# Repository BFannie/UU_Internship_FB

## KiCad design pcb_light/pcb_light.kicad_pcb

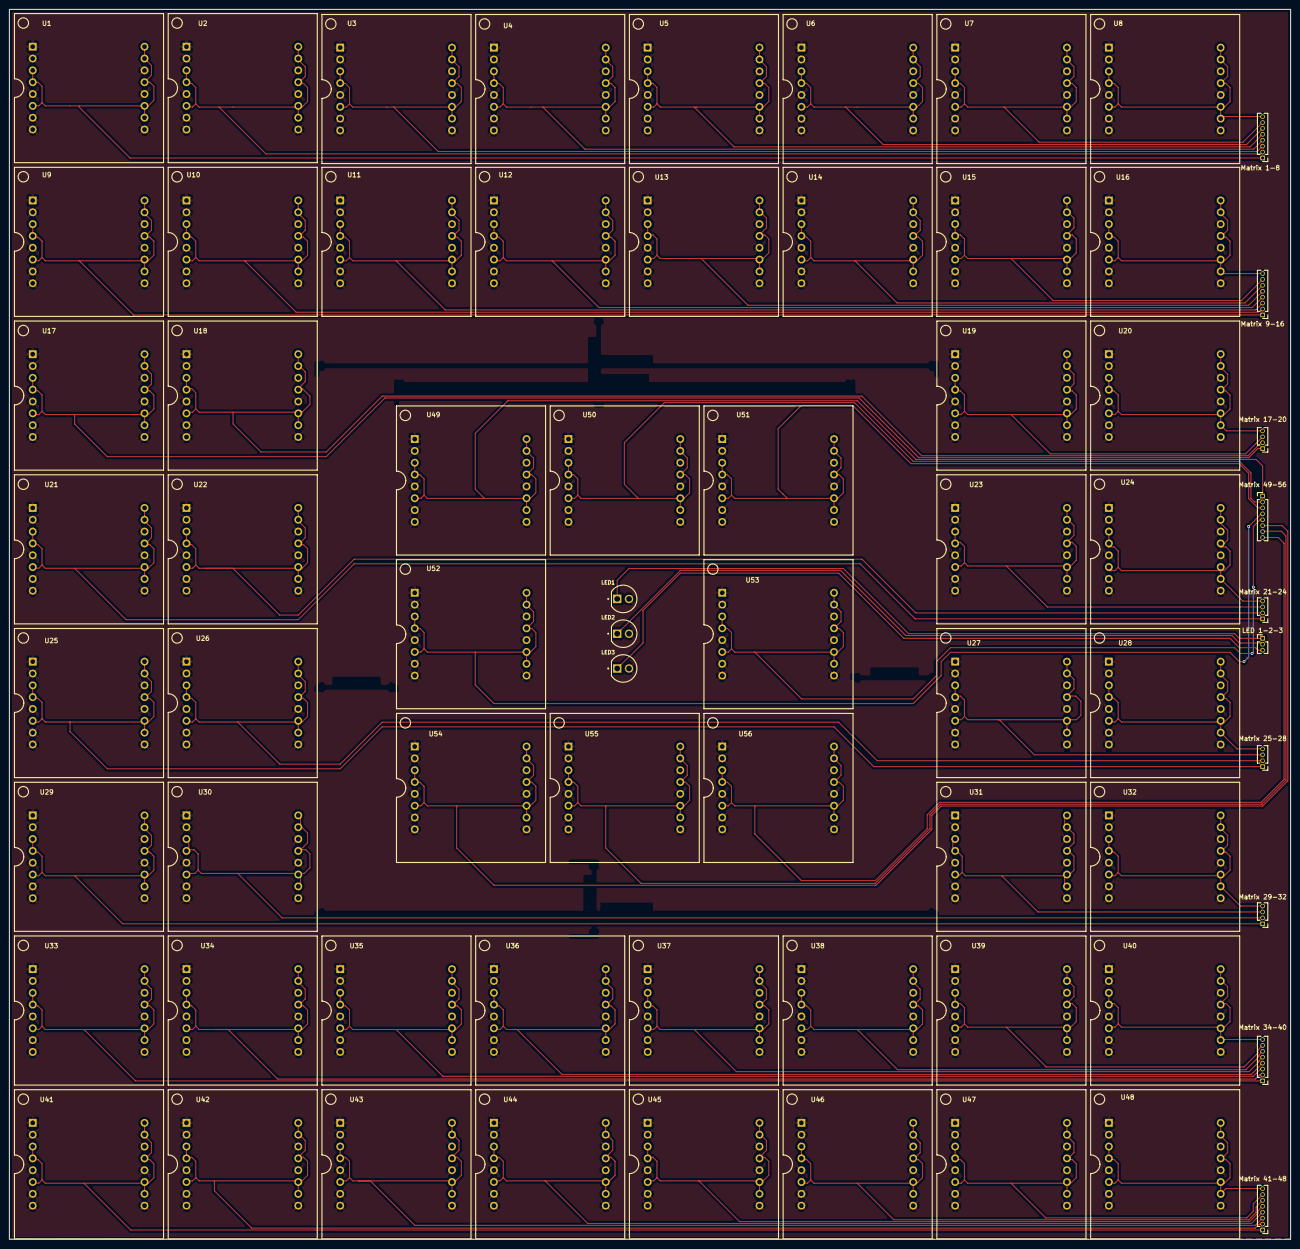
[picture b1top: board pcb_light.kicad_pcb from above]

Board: 2 copper layers, 275.0 x 264.0 mm, 69 parts (0 on the bottom side), 60 nets.

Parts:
 Matrix 1-8,  Matrix 9-16,  Matrix 34-40,  Matrix 41-48,  Matrix 49-56: Conn_01x08_Pin; PinHeader_1x08_P1.27mm_Vertical
 Matrix 17-20: Matrix 17-20; PinHeader_1x04_P1.27mm_Vertical
 Matrix 21-24,  Matrix 25-28,  Matrix 29-32: Conn_01x04_Pin; PinHeader_1x04_P1.27mm_Vertical
LED1, LED2, LED3: L08R5000Q1; LEDRD254W57D500H1070
LED 1-2-3: Conn_01x03_Pin; PinHeader_1x03_P1.27mm_Vertical
U1, U2, U3, U4, U5, U6, U7, U8, U9, U10, U11, U12, U13, U14, U15, U16, U17, U18, U19, U20, U21, U22, U23, U24, U25, U26, U27, U28, U29, U30, U31, U32, U33, U34, U35, U36, U37, U38, U39, U40, U41, U42, U43, U44, U45, U46, U47, U48, U49, U50, U51, U52, U53, U54, U55, U56: 1088BS; LED_1088_Pin_Header

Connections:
GND: LED1.A, LED2.A, LED3.A, U1.1 (C4), U1.2 (C2), U1.5 (C1), U1.7 (C3), U1.8 (C6), U1.9 (C8), U1.12 (C5), U1.14 (C7), U2.1 (C4), U2.2 (C2), U2.5 (C1), U2.7 (C3), U2.8 (C6), U2.9 (C8), U2.12 (C5), U2.14 (C7), U3.1 (C4), U3.2 (C2), U3.5 (C1), U3.7 (C3), U3.8 (C6), U3.9 (C8), U3.12 (C5), U3.14 (C7), U4.1 (C4), U4.2 (C2), U4.5 (C1), U4.7 (C3), U4.8 (C6), U4.9 (C8), U4.12 (C5), U4.14 (C7), U5.1 (C4), U5.2 (C2), U5.5 (C1), U5.7 (C3), U5.8 (C6), U5.9 (C8), U5.12 (C5), U5.14 (C7), U6.1 (C4), U6.2 (C2), U6.5 (C1), U6.7 (C3), U6.8 (C6), U6.9 (C8), U6.12 (C5), U6.14 (C7), U7.1 (C4), U7.2 (C2), U7.5 (C1), U7.7 (C3), U7.8 (C6), U7.9 (C8), U7.12 (C5), U7.14 (C7), U8.1 (C4), U8.2 (C2), U8.5 (C1), U8.7 (C3), U8.8 (C6), U8.9 (C8), U8.12 (C5), U8.14 (C7), U9.1 (C4), U9.2 (C2), U9.5 (C1), U9.7 (C3), U9.8 (C6), U9.9 (C8), U9.12 (C5), U9.14 (C7), U10.1 (C4), U10.2 (C2), U10.5 (C1), U10.7 (C3), U10.8 (C6), U10.9 (C8), U10.12 (C5), U10.14 (C7), U11.1 (C4), U11.2 (C2), U11.5 (C1), U11.7 (C3), U11.8 (C6), U11.9 (C8), U11.12 (C5), U11.14 (C7), U12.1 (C4), U12.2 (C2), U12.5 (C1), U12.7 (C3), U12.8 (C6), U12.9 (C8), U12.12 (C5), U12.14 (C7), U13.1 (C4), U13.2 (C2), U13.5 (C1), U13.7 (C3), U13.8 (C6), U13.9 (C8), U13.12 (C5), U13.14 (C7), U14.1 (C4), U14.2 (C2), U14.5 (C1), U14.7 (C3), U14.8 (C6), U14.9 (C8), U14.12 (C5), U14.14 (C7), U15.1 (C4), U15.2 (C2), U15.5 (C1), U15.7 (C3), U15.8 (C6), U15.9 (C8), U15.12 (C5), U15.14 (C7), U16.1 (C4), U16.2 (C2), U16.5 (C1), U16.7 (C3), U16.8 (C6), U16.9 (C8), U16.12 (C5), U16.14 (C7), U17.1 (C4), U17.2 (C2), U17.5 (C1), U17.7 (C3), U17.8 (C6), U17.9 (C8), U17.12 (C5), U17.14 (C7), U18.1 (C4), U18.2 (C2), U18.5 (C1), U18.7 (C3), U18.8 (C6), U18.9 (C8), U18.12 (C5), U18.14 (C7), U19.1 (C4), U19.2 (C2), U19.5 (C1), U19.7 (C3), U19.8 (C6), U19.9 (C8), U19.12 (C5), U19.14 (C7), U20.1 (C4), U20.2 (C2), U20.5 (C1), U20.7 (C3), U20.8 (C6), U20.9 (C8), U20.12 (C5), U20.14 (C7), U21.1 (C4), U21.2 (C2), U21.5 (C1), U21.7 (C3), U21.8 (C6), U21.9 (C8), U21.12 (C5), U21.14 (C7), U22.1 (C4), U22.2 (C2), U22.5 (C1), U22.7 (C3), U22.8 (C6), U22.9 (C8), U22.12 (C5), U22.14 (C7), U23.1 (C4), U23.2 (C2), U23.5 (C1), U23.7 (C3), U23.8 (C6), U23.9 (C8), U23.12 (C5), U23.14 (C7), U24.1 (C4), U24.2 (C2), U24.5 (C1), U24.7 (C3), U24.8 (C6), U24.9 (C8), U24.12 (C5), U24.14 (C7), U25.1 (C4), U25.2 (C2), U25.5 (C1), U25.7 (C3), U25.8 (C6), U25.9 (C8), U25.12 (C5), U25.14 (C7), U26.1 (C4), U26.2 (C2), U26.5 (C1), U26.7 (C3), U26.8 (C6), U26.9 (C8), U26.12 (C5), U26.14 (C7), U27.1 (C4), U27.2 (C2), U27.5 (C1), U27.7 (C3), U27.8 (C6), U27.9 (C8), U27.12 (C5), U27.14 (C7), U28.1 (C4), U28.2 (C2), U28.5 (C1), U28.7 (C3), U28.8 (C6), U28.9 (C8), U28.12 (C5), U28.14 (C7), U29.1 (C4), U29.2 (C2), U29.5 (C1), U29.7 (C3), U29.8 (C6), U29.9 (C8), U29.12 (C5), U29.14 (C7), U30.1 (C4), U30.2 (C2), U30.5 (C1), U30.7 (C3), U30.8 (C6), U30.9 (C8), U30.12 (C5), U30.14 (C7), U31.1 (C4), U31.2 (C2), U31.5 (C1), U31.7 (C3), U31.8 (C6), U31.9 (C8), U31.12 (C5), U31.14 (C7), U32.1 (C4), U32.2 (C2), U32.5 (C1), U32.7 (C3), U32.8 (C6), U32.9 (C8), U32.12 (C5), U32.14 (C7), U33.1 (C4), U33.2 (C2), U33.5 (C1), U33.7 (C3), U33.8 (C6), U33.9 (C8), U33.12 (C5), U33.14 (C7), U34.1 (C4), U34.2 (C2), U34.5 (C1), U34.7 (C3), U34.8 (C6), U34.9 (C8), U34.12 (C5), U34.14 (C7), U35.1 (C4), U35.2 (C2), U35.5 (C1), U35.7 (C3), U35.8 (C6), U35.9 (C8), U35.12 (C5), U35.14 (C7), U36.1 (C4), U36.2 (C2), U36.5 (C1), U36.7 (C3), U36.8 (C6), U36.9 (C8), U36.12 (C5), U36.14 (C7), U37.1 (C4), U37.2 (C2), U37.5 (C1), U37.7 (C3), U37.8 (C6), U37.9 (C8), U37.12 (C5), U37.14 (C7), U38.1 (C4), U38.2 (C2), U38.5 (C1), U38.7 (C3), U38.8 (C6), U38.9 (C8), U38.12 (C5), U38.14 (C7), U39.1 (C4), U39.2 (C2), U39.5 (C1), U39.7 (C3), U39.8 (C6), U39.9 (C8), U39.12 (C5), U39.14 (C7), U40.1 (C4), U40.2 (C2), U40.5 (C1), U40.7 (C3), U40.8 (C6), U40.9 (C8), U40.12 (C5), U40.14 (C7), U41.1 (C4), U41.2 (C2), U41.5 (C1), U41.7 (C3), U41.8 (C6), U41.9 (C8), U41.12 (C5), U41.14 (C7), U42.1 (C4), U42.2 (C2), U42.5 (C1), U42.7 (C3), U42.8 (C6), U42.9 (C8), U42.12 (C5), U42.14 (C7), U43.1 (C4), U43.2 (C2), U43.5 (C1), U43.7 (C3), U43.8 (C6), U43.9 (C8), U43.12 (C5), U43.14 (C7), U44.1 (C4), U44.2 (C2), U44.5 (C1), U44.7 (C3), U44.8 (C6), U44.9 (C8), U44.12 (C5), U44.14 (C7), U45.1 (C4), U45.2 (C2), U45.5 (C1), U45.7 (C3), U45.8 (C6), U45.9 (C8), U45.12 (C5), U45.14 (C7), U46.1 (C4), U46.2 (C2), U46.5 (C1), U46.7 (C3), U46.8 (C6), U46.9 (C8), U46.12 (C5), U46.14 (C7), U47.1 (C4), U47.2 (C2), U47.5 (C1), U47.7 (C3), U47.8 (C6), U47.9 (C8), U47.12 (C5), U47.14 (C7), U48.1 (C4), U48.2 (C2), U48.5 (C1), U48.7 (C3), U48.8 (C6), U48.9 (C8), U48.12 (C5), U48.14 (C7), U49.1 (C4), U49.2 (C2), U49.5 (C1), U49.7 (C3), U49.8 (C6), U49.9 (C8), U49.12 (C5), U49.14 (C7), U50.1 (C4), U50.2 (C2), U50.5 (C1), U50.7 (C3), U50.8 (C6), U50.9 (C8), U50.12 (C5), U50.14 (C7), U51.1 (C4), U51.2 (C2), U51.5 (C1), U51.7 (C3), U51.8 (C6), U51.9 (C8), U51.12 (C5), U51.14 (C7), U52.1 (C4), U52.2 (C2), U52.5 (C1), U52.7 (C3), U52.8 (C6), U52.9 (C8), U52.12 (C5), U52.14 (C7), U53.1 (C4), U53.2 (C2), U53.5 (C1), U53.7 (C3), U53.8 (C6), U53.9 (C8), U53.12 (C5), U53.14 (C7), U54.1 (C4), U54.2 (C2), U54.5 (C1), U54.7 (C3), U54.8 (C6), U54.9 (C8), U54.12 (C5), U54.14 (C7), U55.1 (C4), U55.2 (C2), U55.5 (C1), U55.7 (C3), U55.8 (C6), U55.9 (C8), U55.12 (C5), U55.14 (C7), U56.1 (C4), U56.2 (C2), U56.5 (C1), U56.7 (C3), U56.8 (C6), U56.9 (C8), U56.12 (C5), U56.14 (C7)
Kath_led1: LED1.C, LED 1-2-3.1
Kath_led2: LED2.C, LED 1-2-3.2
Kath_led3: LED3.C, LED 1-2-3.3
kath_1: Matrix 1-8.1, U1.3 (R2), U1.4 (R3), U1.6 (R5), U1.10 (R4), U1.11 (R6), U1.13 (R1), U1.15 (R7), U1.16 (R8)
kath_2: Matrix 1-8.2, U2.3 (R2), U2.4 (R3), U2.6 (R5), U2.10 (R4), U2.11 (R6), U2.13 (R1), U2.15 (R7), U2.16 (R8)
kath_3: Matrix 1-8.3, U3.3 (R2), U3.4 (R3), U3.6 (R5), U3.10 (R4), U3.11 (R6), U3.13 (R1), U3.15 (R7), U3.16 (R8)
kath_4: Matrix 1-8.4, U4.3 (R2), U4.4 (R3), U4.6 (R5), U4.10 (R4), U4.11 (R6), U4.13 (R1), U4.15 (R7), U4.16 (R8)
kath_5: Matrix 1-8.5, U5.3 (R2), U5.4 (R3), U5.6 (R5), U5.10 (R4), U5.11 (R6), U5.13 (R1), U5.15 (R7), U5.16 (R8)
kath_6: Matrix 1-8.6, U6.3 (R2), U6.4 (R3), U6.6 (R5), U6.10 (R4), U6.11 (R6), U6.13 (R1), U6.15 (R7), U6.16 (R8)
kath_7: Matrix 1-8.7, U7.3 (R2), U7.4 (R3), U7.6 (R5), U7.10 (R4), U7.11 (R6), U7.13 (R1), U7.15 (R7), U7.16 (R8)
kath_8: Matrix 1-8.8, U8.3 (R2), U8.4 (R3), U8.6 (R5), U8.10 (R4), U8.11 (R6), U8.13 (R1), U8.15 (R7), U8.16 (R8)
kath_9: Matrix 9-16.1, U9.3 (R2), U9.4 (R3), U9.6 (R5), U9.10 (R4), U9.11 (R6), U9.13 (R1), U9.15 (R7), U9.16 (R8)
kath_10: Matrix 9-16.2, U10.3 (R2), U10.4 (R3), U10.6 (R5), U10.10 (R4), U10.11 (R6), U10.13 (R1), U10.15 (R7), U10.16 (R8)
kath_11: Matrix 9-16.3, U11.3 (R2), U11.4 (R3), U11.6 (R5), U11.10 (R4), U11.11 (R6), U11.13 (R1), U11.15 (R7), U11.16 (R8)
kath_12: Matrix 9-16.4, U12.3 (R2), U12.4 (R3), U12.6 (R5), U12.10 (R4), U12.11 (R6), U12.13 (R1), U12.15 (R7), U12.16 (R8)
kath_13: Matrix 9-16.5, U13.3 (R2), U13.4 (R3), U13.6 (R5), U13.10 (R4), U13.11 (R6), U13.13 (R1), U13.15 (R7), U13.16 (R8)
kath_14: Matrix 9-16.6, U14.3 (R2), U14.4 (R3), U14.6 (R5), U14.10 (R4), U14.11 (R6), U14.13 (R1), U14.15 (R7), U14.16 (R8)
kath_15: Matrix 9-16.7, U15.3 (R2), U15.4 (R3), U15.6 (R5), U15.10 (R4), U15.11 (R6), U15.13 (R1), U15.15 (R7), U15.16 (R8)
kath_16: Matrix 9-16.8, U16.3 (R2), U16.4 (R3), U16.6 (R5), U16.10 (R4), U16.11 (R6), U16.13 (R1), U16.15 (R7), U16.16 (R8)
kath_17: Matrix 17-20.1, U17.3 (R2), U17.4 (R3), U17.6 (R5), U17.10 (R4), U17.11 (R6), U17.13 (R1), U17.15 (R7), U17.16 (R8)
kath_18: Matrix 17-20.2, U18.3 (R2), U18.4 (R3), U18.6 (R5), U18.10 (R4), U18.11 (R6), U18.13 (R1), U18.15 (R7), U18.16 (R8)
kath_19: Matrix 17-20.3, U19.3 (R2), U19.4 (R3), U19.6 (R5), U19.10 (R4), U19.11 (R6), U19.13 (R1), U19.15 (R7), U19.16 (R8)
kath_20: Matrix 17-20.4, U20.3 (R2), U20.4 (R3), U20.6 (R5), U20.10 (R4), U20.11 (R6), U20.13 (R1), U20.15 (R7), U20.16 (R8)
kath_21: Matrix 21-24.1, U21.3 (R2), U21.4 (R3), U21.6 (R5), U21.10 (R4), U21.11 (R6), U21.13 (R1), U21.15 (R7), U21.16 (R8)
kath_22: Matrix 21-24.2, U22.3 (R2), U22.4 (R3), U22.6 (R5), U22.10 (R4), U22.11 (R6), U22.13 (R1), U22.15 (R7), U22.16 (R8)
kath_23: Matrix 21-24.3, U23.3 (R2), U23.4 (R3), U23.6 (R5), U23.10 (R4), U23.11 (R6), U23.13 (R1), U23.15 (R7), U23.16 (R8)
kath_24: Matrix 21-24.4, U24.3 (R2), U24.4 (R3), U24.6 (R5), U24.10 (R4), U24.11 (R6), U24.13 (R1), U24.15 (R7), U24.16 (R8)
kath_25: Matrix 25-28.1, U25.3 (R2), U25.4 (R3), U25.6 (R5), U25.10 (R4), U25.11 (R6), U25.13 (R1), U25.15 (R7), U25.16 (R8)
kath_26: Matrix 25-28.2, U26.3 (R2), U26.4 (R3), U26.6 (R5), U26.10 (R4), U26.11 (R6), U26.13 (R1), U26.15 (R7), U26.16 (R8)
kath_27: Matrix 25-28.3, U27.3 (R2), U27.4 (R3), U27.6 (R5), U27.10 (R4), U27.11 (R6), U27.13 (R1), U27.15 (R7), U27.16 (R8)
kath_28: Matrix 25-28.4, U28.3 (R2), U28.4 (R3), U28.6 (R5), U28.10 (R4), U28.11 (R6), U28.13 (R1), U28.15 (R7), U28.16 (R8)
kath_29: Matrix 29-32.1, U29.3 (R2), U29.4 (R3), U29.6 (R5), U29.10 (R4), U29.11 (R6), U29.13 (R1), U29.15 (R7), U29.16 (R8)
kath_30: Matrix 29-32.2, U30.3 (R2), U30.4 (R3), U30.6 (R5), U30.10 (R4), U30.11 (R6), U30.13 (R1), U30.15 (R7), U30.16 (R8)
kath_31: Matrix 29-32.3, U31.3 (R2), U31.4 (R3), U31.6 (R5), U31.10 (R4), U31.11 (R6), U31.13 (R1), U31.15 (R7), U31.16 (R8)
kath_32: Matrix 29-32.4, U32.3 (R2), U32.4 (R3), U32.6 (R5), U32.10 (R4), U32.11 (R6), U32.13 (R1), U32.15 (R7), U32.16 (R8)
kath_33: Matrix 34-40.1, U33.3 (R2), U33.4 (R3), U33.6 (R5), U33.10 (R4), U33.11 (R6), U33.13 (R1), U33.15 (R7), U33.16 (R8)
kath_34: Matrix 34-40.2, U34.3 (R2), U34.4 (R3), U34.6 (R5), U34.10 (R4), U34.11 (R6), U34.13 (R1), U34.15 (R7), U34.16 (R8)
kath_35: Matrix 34-40.3, U35.3 (R2), U35.4 (R3), U35.6 (R5), U35.10 (R4), U35.11 (R6), U35.13 (R1), U35.15 (R7), U35.16 (R8)
kath_36: Matrix 34-40.4, U36.3 (R2), U36.4 (R3), U36.6 (R5), U36.10 (R4), U36.11 (R6), U36.13 (R1), U36.15 (R7), U36.16 (R8)
kath_37: Matrix 34-40.5, U37.3 (R2), U37.4 (R3), U37.6 (R5), U37.10 (R4), U37.11 (R6), U37.13 (R1), U37.15 (R7), U37.16 (R8)
kath_38: Matrix 34-40.6, U38.3 (R2), U38.4 (R3), U38.6 (R5), U38.10 (R4), U38.11 (R6), U38.13 (R1), U38.15 (R7), U38.16 (R8)
kath_39: Matrix 34-40.7, U39.3 (R2), U39.4 (R3), U39.6 (R5), U39.10 (R4), U39.11 (R6), U39.13 (R1), U39.15 (R7), U39.16 (R8)
kath_40: Matrix 34-40.8, U40.3 (R2), U40.4 (R3), U40.6 (R5), U40.10 (R4), U40.11 (R6), U40.13 (R1), U40.15 (R7), U40.16 (R8)
kath_41: Matrix 41-48.1, U41.3 (R2), U41.4 (R3), U41.6 (R5), U41.10 (R4), U41.11 (R6), U41.13 (R1), U41.15 (R7), U41.16 (R8)
kath_42: Matrix 41-48.2, U42.3 (R2), U42.4 (R3), U42.6 (R5), U42.10 (R4), U42.11 (R6), U42.13 (R1), U42.15 (R7), U42.16 (R8)
kath_43: Matrix 41-48.3, U43.3 (R2), U43.4 (R3), U43.6 (R5), U43.10 (R4), U43.11 (R6), U43.13 (R1), U43.15 (R7), U43.16 (R8)
kath_44: Matrix 41-48.4, U44.3 (R2), U44.4 (R3), U44.6 (R5), U44.10 (R4), U44.11 (R6), U44.13 (R1), U44.15 (R7), U44.16 (R8)
kath_45: Matrix 41-48.5, U45.3 (R2), U45.4 (R3), U45.6 (R5), U45.10 (R4), U45.11 (R6), U45.13 (R1), U45.15 (R7), U45.16 (R8)
kath_46: Matrix 41-48.6, U46.3 (R2), U46.4 (R3), U46.6 (R5), U46.10 (R4), U46.11 (R6), U46.13 (R1), U46.15 (R7), U46.16 (R8)
kath_47: Matrix 41-48.7, U47.3 (R2), U47.4 (R3), U47.6 (R5), U47.10 (R4), U47.11 (R6), U47.13 (R1), U47.15 (R7), U47.16 (R8)
kath_48: Matrix 41-48.8, U48.3 (R2), U48.4 (R3), U48.6 (R5), U48.10 (R4), U48.11 (R6), U48.13 (R1), U48.15 (R7), U48.16 (R8)
kath_49: Matrix 49-56.1, U49.3 (R2), U49.4 (R3), U49.6 (R5), U49.10 (R4), U49.11 (R6), U49.13 (R1), U49.15 (R7), U49.16 (R8)
kath_50: Matrix 49-56.2, U50.3 (R2), U50.4 (R3), U50.6 (R5), U50.10 (R4), U50.11 (R6), U50.13 (R1), U50.15 (R7), U50.16 (R8)
kath_51: Matrix 49-56.3, U51.3 (R2), U51.4 (R3), U51.6 (R5), U51.10 (R4), U51.11 (R6), U51.13 (R1), U51.15 (R7), U51.16 (R8)
kath_52: Matrix 49-56.4, U52.3 (R2), U52.4 (R3), U52.6 (R5), U52.10 (R4), U52.11 (R6), U52.13 (R1), U52.15 (R7), U52.16 (R8)
kath_53: Matrix 49-56.5, U53.3 (R2), U53.4 (R3), U53.6 (R5), U53.10 (R4), U53.11 (R6), U53.13 (R1), U53.15 (R7), U53.16 (R8)
kath_54: Matrix 49-56.6, U54.3 (R2), U54.4 (R3), U54.6 (R5), U54.10 (R4), U54.11 (R6), U54.13 (R1), U54.15 (R7), U54.16 (R8)
kath_55: Matrix 49-56.7, U55.3 (R2), U55.4 (R3), U55.6 (R5), U55.10 (R4), U55.11 (R6), U55.13 (R1), U55.15 (R7), U55.16 (R8)
kath_56: Matrix 49-56.8, U56.3 (R2), U56.4 (R3), U56.6 (R5), U56.10 (R4), U56.11 (R6), U56.13 (R1), U56.15 (R7), U56.16 (R8)
